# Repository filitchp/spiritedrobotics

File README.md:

# SantaBarBot Progress 

##Jan 21 2013
	
### Done:
- Breadboarded avr,
- Driving LED strip
- Driving PWM

### ToDo:
- Ron: protocol
- Dan: schematic
- Ryan: state machine + motor driver on breadboard

- Get crystal
- Raspi,
- Webserver
- Communication working
- Board Layout

## Nov 18 2012

Todo:
- Figure out motor driving
	- PWM direction or enable
- Start prototyping on the avr
	- Get powersupply and breadboard header
- Figure out if we want 1 or 2 uarts
	- Driving uart with raspberry pi
		- Can we directly use the onboard ethernet?
- Select avr chip (based on requirements)
	- Order a few of the them in a dip package for prototyping
- Meet Tuesday at 11.
	- Email invite to everyone
		
- Get everyone on google code group
	- Setup email notifications when commits made

- Setup irc chatroom.

- Ideas:
	
	- Use single bus with a buffer that can be disabled
		- Buffer keep signal strong over long distances
		- Enable allows us to determine the order of towers on the network
	- Semi-circle tower configuration
	- Towers modular
	- Sync spray to music / lights (bellagio)
	- Lazy susan to move cup into firing range and to customer
		- Doesn't have to be full circle. could be single beam with counter weight or multiple beams with cups on end (spokes of tire)spoke could have hole that cup would drop into
		- Rubber washer to set height and adjut for different cup sizes
	- Cup loader could drop cups on to lazy susan, or uses arm to grab cup and set it on the lazy susan
	
	- Ice machine? relay to control the dispensing of ice?
		- Digital scale to measure how much ice?

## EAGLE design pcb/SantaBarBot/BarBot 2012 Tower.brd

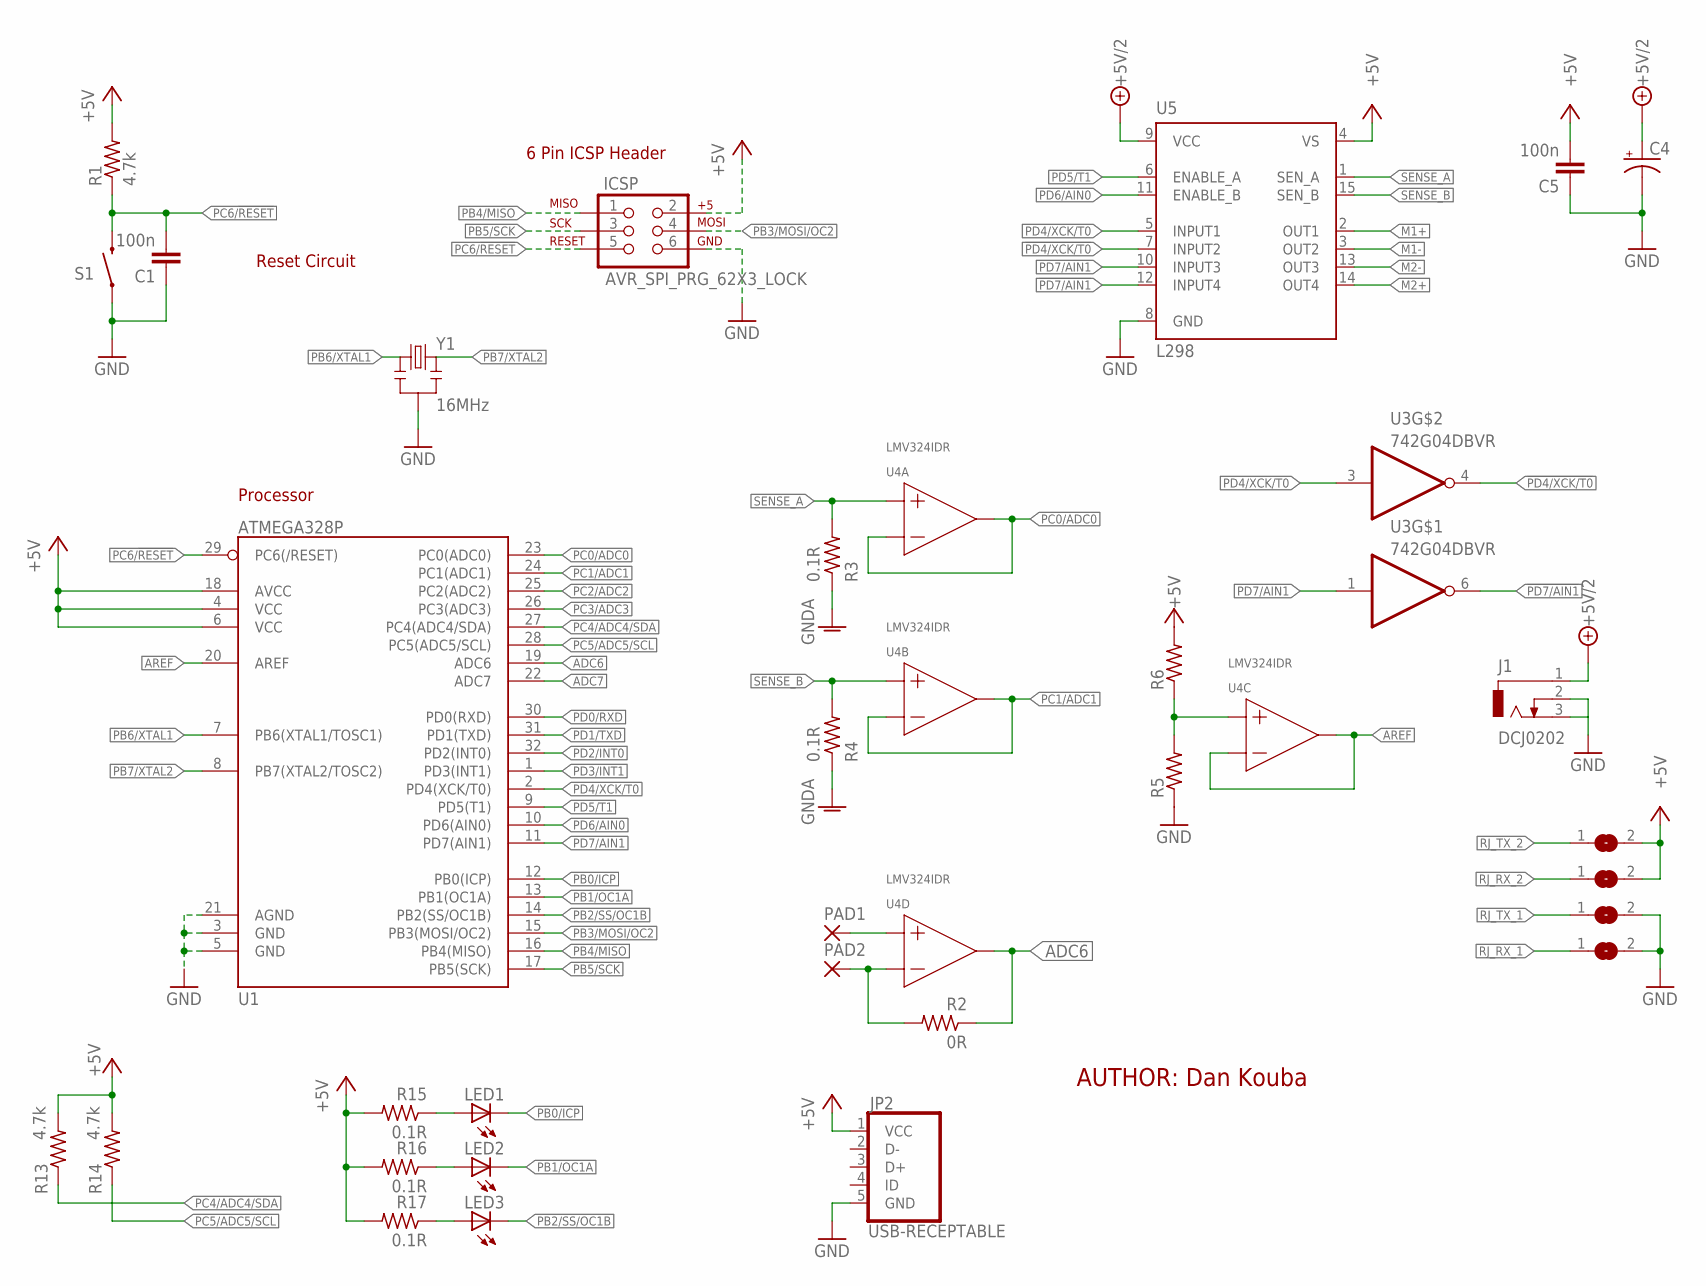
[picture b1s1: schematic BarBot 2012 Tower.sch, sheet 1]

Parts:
C1, C5: 100n; C0805
C4: CPOL-USE3.5-8; E3,5-8
ICSP: AVR_SPI_PRG_62X3_LOCK; 2X3_LOCK
J1: DCJ0202
JP2: USB-RECEPTABLE; FCI-10103594-0001LF
LED1, LED2, LED3: LEDCHIPLED_0805; CHIPLED_0805
PAD1, PAD2: 1,6/0,8
R1: 4.7k; R0805
R2: 0R; R0805; DIGIKEY_PN RHM.10MCT-ND
R3, R4, R15, R16, R17: 0.1R; R0805; DIGIKEY_PN RHM.10MCT-ND
R5, R6: R-US_R0805; R0805
R13, R14: 4.7k; R0805; DIGIKEY_PN RHM.10MCT-ND
S1: SWITCH-MOMENTARY-2PTH; TACTILE-PTH
SJ1, SJ2, SJ3, SJ4: SJ
U1: ATMEGA328P; TQFP32-08
U3: 742G04DBVR; DBV_R-PDSO-G6
U4: LMV324IDR; SO14
U5: L298; MULTIWATT-15
Y1: 16MHz; RESONATOR-SMD

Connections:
!PD4/XCK/T0: U3.4 (O), U5.7 (INPUT2)
!PD7/AIN1: U3.6 (O), U5.12 (INPUT4)
+5V: C5.2, ICSP.2, JP2.1 (VCC), R1.2, R6.2, R13.2, R14.2, R15.2, R16.2, R17.2, SJ3.2, SJ4.2, U1.4 (VCC), U1.6 (VCC), U1.18 (AVCC), U5.4 (VS); also elsewhere on the board
+5V/2: C4.+, J1.1, U5.9 (VCC); also elsewhere on the board
ADC6: R2.1, U1.19 (ADC6), U4.14 (OUT)
ADC7: U1.22 (ADC7)
AREF: U1.20 (AREF), U4.8 (OUT), U4.9 (-IN)
GND: C1.1, C4.-, C5.1, ICSP.6, J1.2, J1.3, JP2.5 (GND), R3.1, R4.1, R5.1, S1.1, SJ1.2, SJ2.2, U1.3 (GND), U1.5 (GND), U1.21 (AGND), U5.8 (GND), Y1.2; also elsewhere on the board
M1+: U5.2 (OUT1); also elsewhere on the board
M1-: U5.3 (OUT2); also elsewhere on the board
M2+: U5.14 (OUT4); also elsewhere on the board
M2-: U5.13 (OUT3); also elsewhere on the board
unnamed: LED1.A, R15.1
unnamed: PAD2.1, R2.2, U4.13 (-IN)
unnamed: LED2.A, R16.1
unnamed: LED3.A, R17.1
unnamed: R5.2, R6.1, U4.10 (+IN)
PB0/ICP: LED1.C, U1.12 (PB0(ICP))
PB1/OC1A: LED2.C, U1.13 (PB1(OC1A))
PB2/SS/OC1B: LED3.C, U1.14 (PB2(SS/OC1B))
PB3/MOSI/OC2: ICSP.4, U1.15 (PB3(MOSI/OC2))
PB4/MISO: ICSP.1, U1.16 (PB4(MISO)); also elsewhere on the board
PB5/SCK: ICSP.3, U1.17 (PB5(SCK)); also elsewhere on the board
PB6/XTAL1: U1.7 (PB6(XTAL1/TOSC1)), Y1.1
PB7/XTAL2: U1.8 (PB7(XTAL2/TOSC2)), Y1.3
PC0/ADC0: U1.23 (PC0(ADC0)), U4.1 (OUT), U4.2 (-IN)
PC1/ADC1: U1.24 (PC1(ADC1)), U4.6 (-IN), U4.7 (OUT)
PC2/ADC2: U1.25 (PC2(ADC2))
PC3/ADC3: U1.26 (PC3(ADC3))
PC4/ADC4/SDA: R13.1, U1.27 (PC4(ADC4/SDA))
PC5/ADC5/SCL: R14.1, U1.28 (PC5(ADC5/SCL))
PC6/!RESET: C1.2, ICSP.5, R1.1, S1.3 (2), U1.29 (PC6(/RESET))
PD0/RXD: U1.30 (PD0(RXD)); also elsewhere on the board
PD1/TXD: U1.31 (PD1(TXD)); also elsewhere on the board
PD2/INT0: U1.32 (PD2(INT0))
PD3/INT1: U1.1 (PD3(INT1))
PD4/XCK/T0: U1.2 (PD4(XCK/T0)), U3.3 (I), U5.5 (INPUT1)
PD5/T1: U1.9 (PD5(T1)), U5.6 (ENABLE_A)
PD6/AIN0: U1.10 (PD6(AIN0)), U5.11 (ENABLE_B)
PD7/AIN1: U1.11 (PD7(AIN1)), U3.1 (I), U5.10 (INPUT3)
RJ_RX_1: SJ2.1; also elsewhere on the board
RJ_RX_2: SJ4.1; also elsewhere on the board
RJ_TX_1: SJ1.1; also elsewhere on the board
RJ_TX_2: SJ3.1; also elsewhere on the board
SENSE_A: R3.2, U4.3 (+IN), U5.1 (SEN_A)
SENSE_B: R4.2, U4.5 (+IN), U5.15 (SEN_B)
TP1: PAD1.1, U4.12 (+IN)

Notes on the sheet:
Reset Circuit
6 Pin ICSP Header
Processor
AUTHOR: Dan Kouba

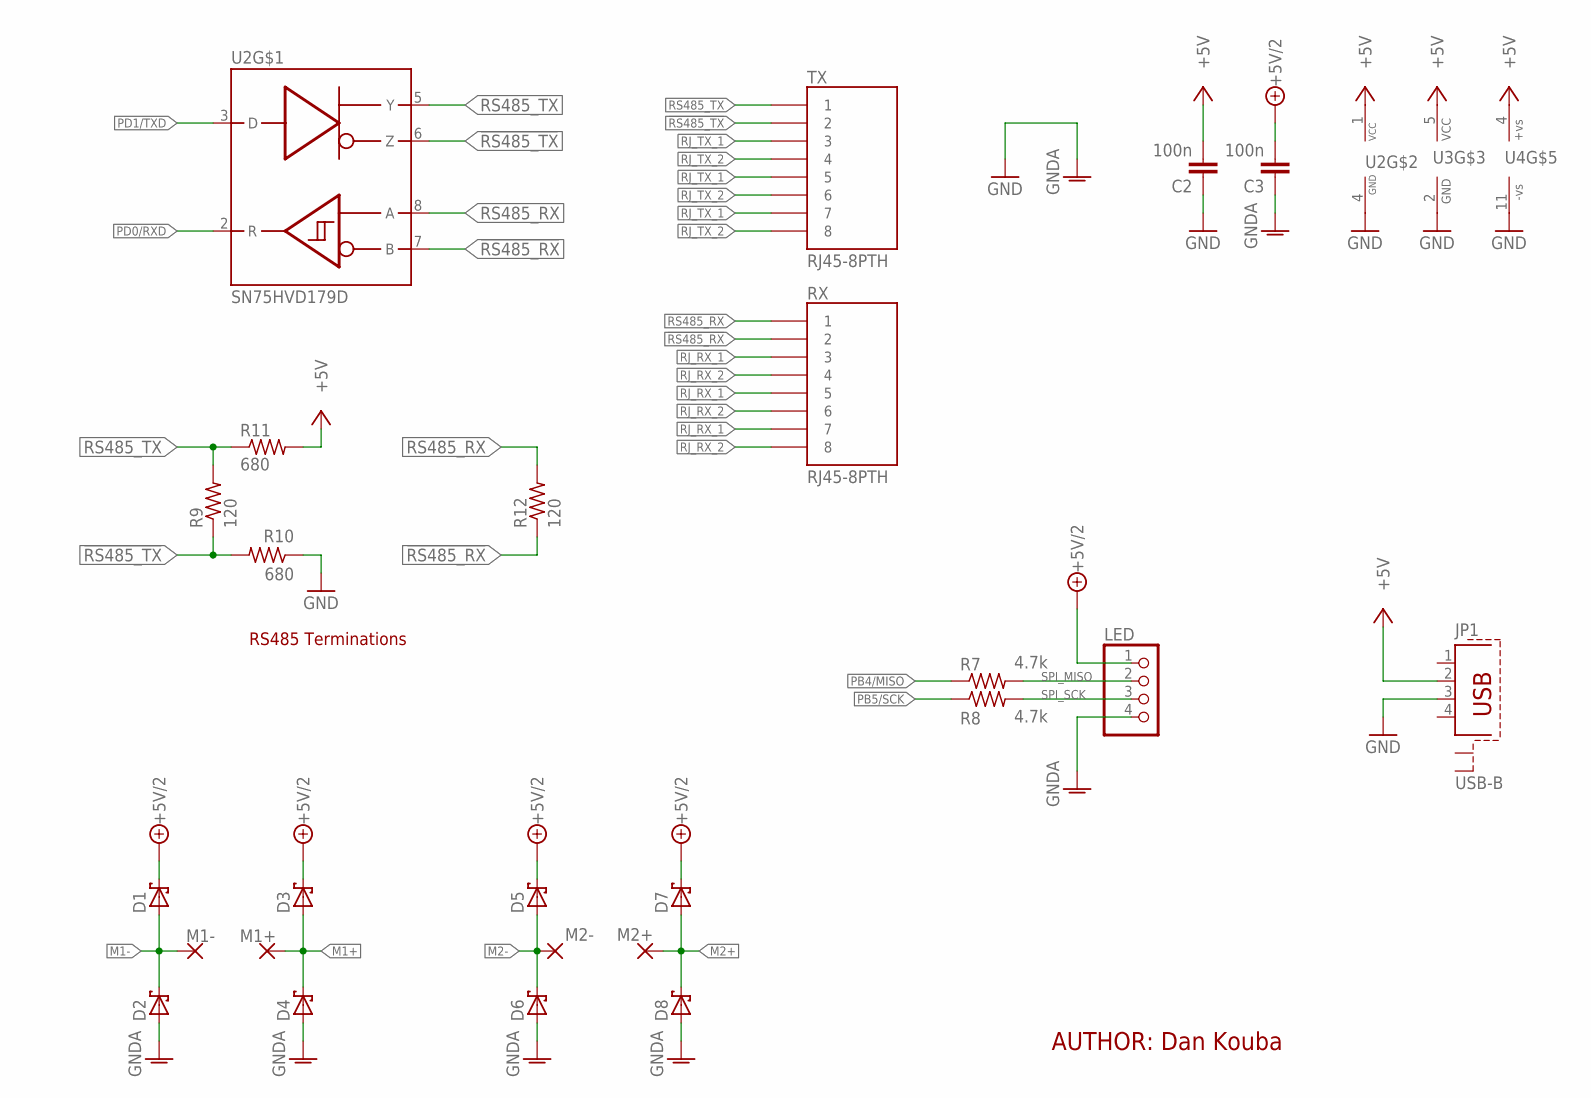
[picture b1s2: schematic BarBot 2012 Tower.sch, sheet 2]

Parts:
C2, C3: 100n; C0805
D1, D2, D3, D4, D5, D6, D7, D8: SCHOTTKY-DIODESMD; SMB; DIGIKEY_PN S320FSCT-ND
JP1: USB-B; PN61729-S
LED: PINHD-1X4; 1X04
M1+, M1-, M2+, M2-: 3,81/1,1
R7, R8: 4.7k; R0805
R9, R12: 120; R0805
R10, R11: 680; R0805
RX: RJ45-8PTH; RJ45-8
TX: RJ45-8PTH; RJ45-8
U2: SN75HVD179D; SO-08
U3: 742G04DBVR; DBV_R-PDSO-G6
U4: LMV324IDR; SO14

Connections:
!RS485_RX: R12.1, RX.2, U2.7 (B)
!RS485_TX: R9.1, R10.2, TX.2, U2.6 (Z)
+5V: C2.2, JP1.2, R11.2, U2.1 (VCC), U3.5 (VCC), U4.4 (+VS); also elsewhere on the board
+5V/2: C3.2, D1.C, D3.C, D5.C, D7.C, LED.1; also elsewhere on the board
GND: C2.1, C3.1, D2.A, D4.A, D6.A, D8.A, JP1.3, LED.4, R10.1, U2.4 (GND), U3.2 (GND), U4.11 (-VS); also elsewhere on the board
M1+: D3.A, D4.C, M1+.1; also elsewhere on the board
M1-: D1.A, D2.C, M1-.1; also elsewhere on the board
M2+: D7.A, D8.C, M2+.1; also elsewhere on the board
M2-: D5.A, D6.C, M2-.1; also elsewhere on the board
PB4/MISO: R7.1; also elsewhere on the board
PB5/SCK: R8.1; also elsewhere on the board
PD0/RXD: U2.2 (R); also elsewhere on the board
PD1/TXD: U2.3 (D); also elsewhere on the board
RJ_RX_1: RX.3, RX.5, RX.7; also elsewhere on the board
RJ_RX_2: RX.4, RX.6, RX.8; also elsewhere on the board
RJ_TX_1: TX.3, TX.5, TX.7; also elsewhere on the board
RJ_TX_2: TX.4, TX.6, TX.8; also elsewhere on the board
RS485_RX: R12.2, RX.1, U2.8 (A)
RS485_TX: R9.2, R11.1, TX.1, U2.5 (Y)
SPI_MISO: LED.2, R7.2
SPI_SCK: LED.3, R8.2

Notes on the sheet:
RS485 Terminations
AUTHOR: Dan Kouba

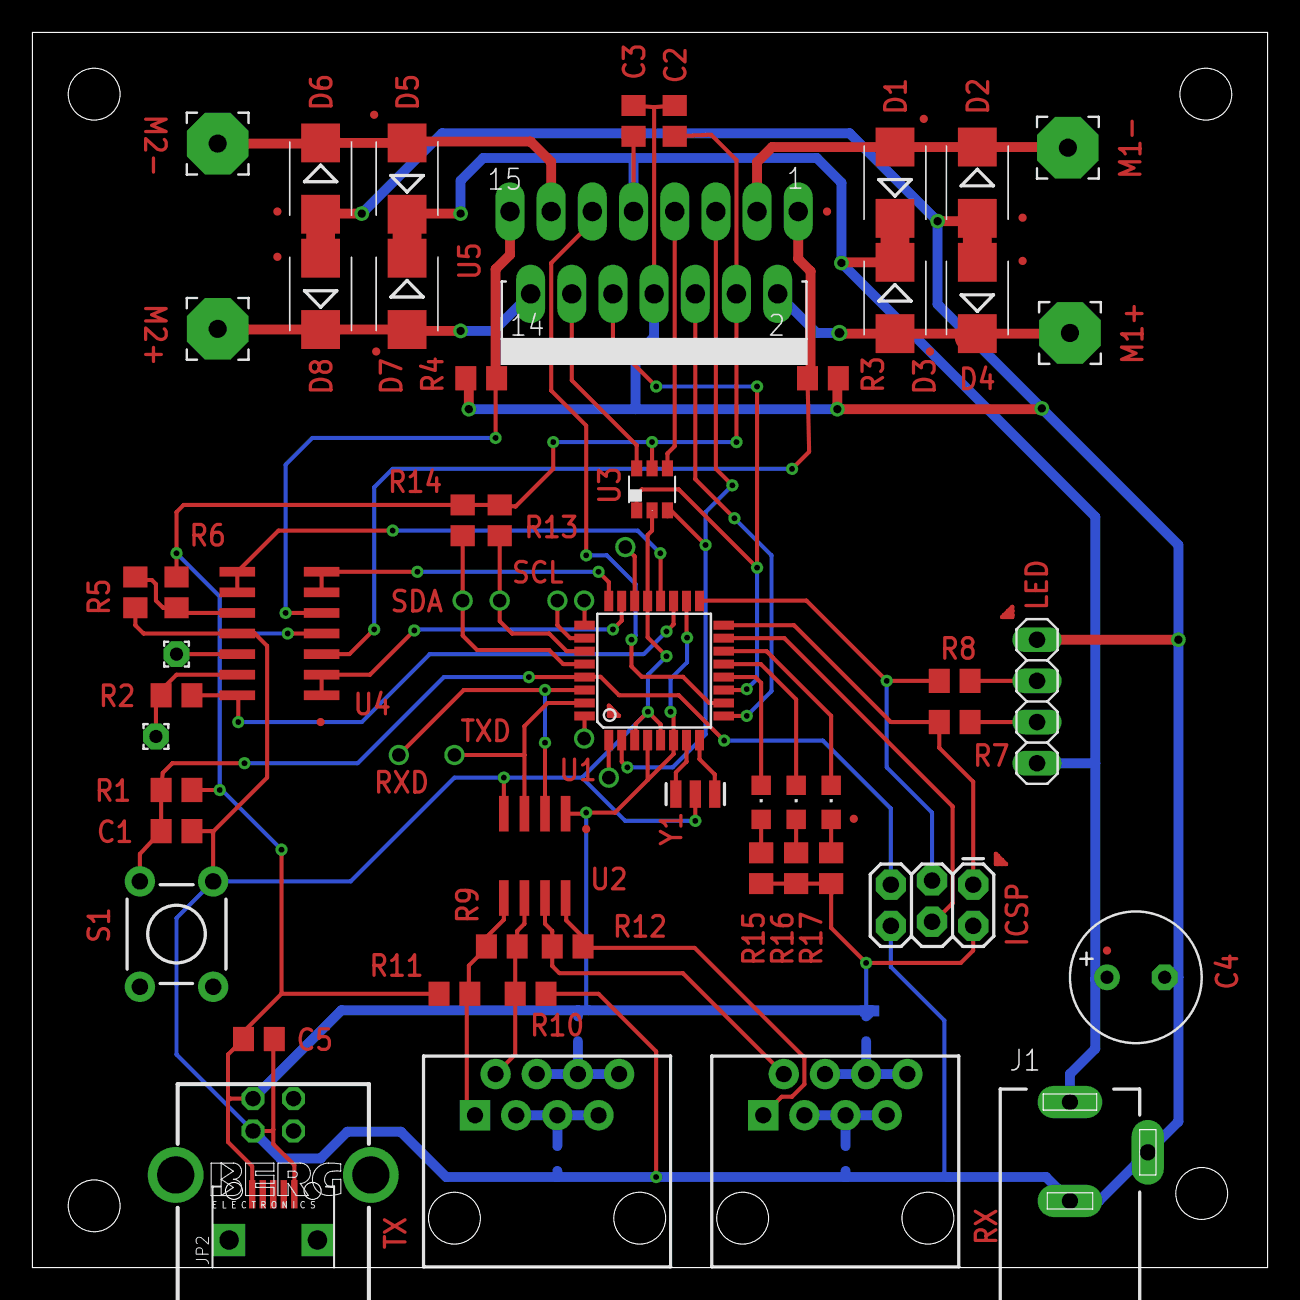
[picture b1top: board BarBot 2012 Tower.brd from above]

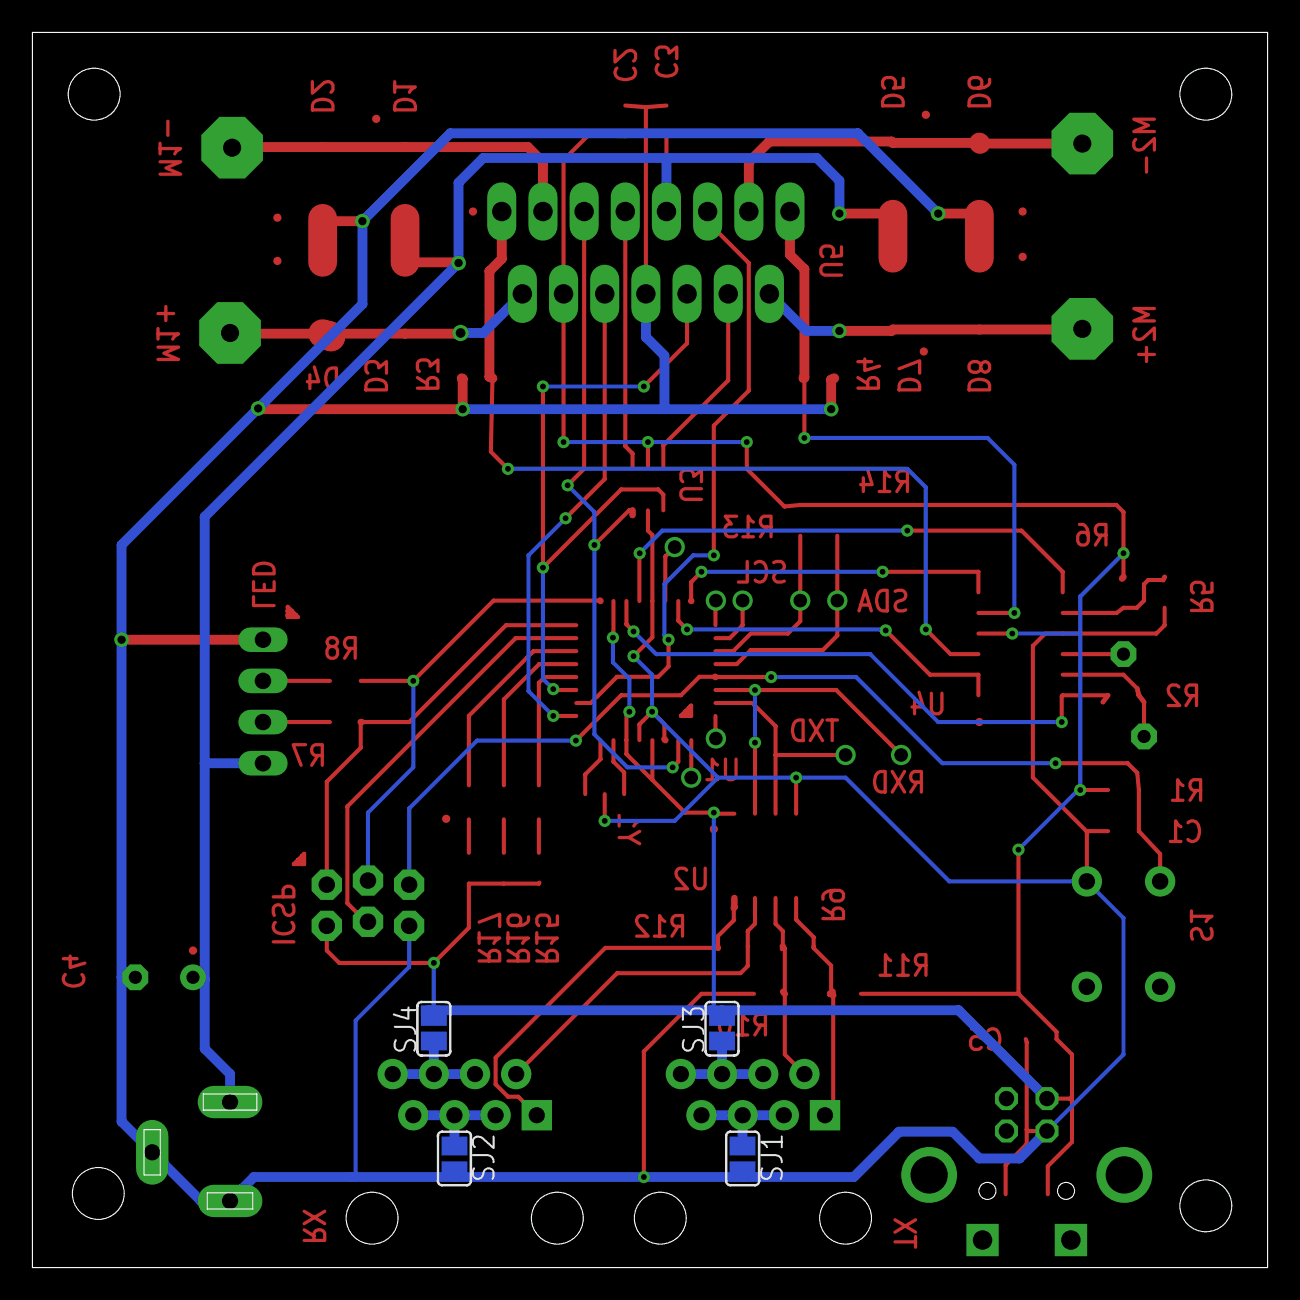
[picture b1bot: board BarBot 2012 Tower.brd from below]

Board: 2 copper layers, 76.2 x 76.2 mm, 57 parts (4 on the bottom side), 48 nets.

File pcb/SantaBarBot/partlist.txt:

Partlist

Exported from BarBot 2012 Tower.sch at 2/10/2013 10:12:03 PM

EAGLE Version 6.3.0 Copyright (c) 1988-2012 CadSoft

Assembly variant: 

Part     Value                 Device                Package         Library                    Sheet

C1       100n                  C-EUC0805             C0805           rcl                        1
C2       100n                  C-EUC0805             C0805           rcl                        2
C3       100n                  C-EUC0805             C0805           rcl                        2
C4                             CPOL-USE3.5-8         E3,5-8          rcl                        1
C5       100n                  C-EUC0805             C0805           rcl                        1
D1                             SCHOTTKY-DIODESMD     SMB             diode                      2
D2                             SCHOTTKY-DIODESMD     SMB             diode                      2
D3                             SCHOTTKY-DIODESMD     SMB             diode                      2
D4                             SCHOTTKY-DIODESMD     SMB             diode                      2
D5                             SCHOTTKY-DIODESMD     SMB             diode                      2
D6                             SCHOTTKY-DIODESMD     SMB             diode                      2
D7                             SCHOTTKY-DIODESMD     SMB             diode                      2
D8                             SCHOTTKY-DIODESMD     SMB             diode                      2
ICSP     AVR_SPI_PRG_62X3_LOCK AVR_SPI_PRG_62X3_LOCK 2X3_LOCK        SparkFun-Connectors        1
J2       POWER_JACKSLT         POWER_JACKSLT         POWER_JACK_SLOT SparkFun-Connectors        2
JP1      USB-B                 PN61729-S             PN61729-S       con-berg                   2
LED                            PINHD-1X4             1X04            pinhead                    2
LED1                           LEDCHIPLED_0805       CHIPLED_0805    led                        1
LED2                           LEDCHIPLED_0805       CHIPLED_0805    led                        1
LED3                           LEDCHIPLED_0805       CHIPLED_0805    led                        1
M1+                            3,81/1,1              3,81/1,1        wirepad                    2
M1-                            3,81/1,1              3,81/1,1        wirepad                    2
M2+                            3,81/1,1              3,81/1,1        wirepad                    2
M2-                            3,81/1,1              3,81/1,1        wirepad                    2
PAD1                           1,6/0,8               1,6/0,8         wirepad                    1
PAD2                           1,6/0,8               1,6/0,8         wirepad                    1
R1       4.7k                  R-US_R0805            R0805           rcl                        1
R2       0R                    R-US_R0805            R0805           rcl                        1
R3       0.1R                  R-US_R0805            R0805           rcl                        1
R4       0.1R                  R-US_R0805            R0805           rcl                        1
R5                             R-US_R0805            R0805           rcl                        1
R6                             R-US_R0805            R0805           rcl                        1
R7       4.7k                  R-US_R0805            R0805           rcl                        2
R8       4.7k                  R-US_R0805            R0805           rcl                        2
R9       120                   R-US_R0805            R0805           rcl                        2
R10      680                   R-US_R0805            R0805           rcl                        2
R11      680                   R-US_R0805            R0805           rcl                        2
R12      120                   R-US_R0805            R0805           rcl                        2
R13      4.7k                  R-US_R0805            R0805           rcl                        1
R14      4.7k                  R-US_R0805            R0805           rcl                        1
R15      0.1R                  R-US_R0805            R0805           rcl                        1
R16      0.1R                  R-US_R0805            R0805           rcl                        1
R17      0.1R                  R-US_R0805            R0805           rcl                        1
RX       RJ45-8PTH             RJ45-8PTH             RJ45-8          SparkFun-Connectors        2
S1       SWITCH-MOMENTARY-2PTH SWITCH-MOMENTARY-2PTH TACTILE-PTH     SparkFun-Electromechanical 1
TX       RJ45-8PTH             RJ45-8PTH             RJ45-8          SparkFun-Connectors        2
U1       ATMEGA328P            ATMEGA328_SMT         TQFP32-08       SparkFun-DigitalIC         1
U2       SN75HVD179D           SN75HVD179D           SO-08           texas                      2
U3       742G04DBVR            742G04DBVR            DBV_R-PDSO-G6   74xx-little-us             1
U4       LMV324IDR             LMV324IDR             SO14            bb_parts_OpAmp             1
U5       L298                  L298                  MULTIWATT-15    st-microelectronics        1
Y1       16MHz                 RESONATOR16MHZ        RESONATOR-SMD   SparkFun-FreqCtrl          1

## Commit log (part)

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2013-01-28 removed os x files
2013-01-28 adding drink json file
2013-01-28 Adding menus barebones
2013-01-28 minor styling mods
2013-01-28 Added boost example HTTP server files
2013-01-28 Removing rendered alert
2013-01-28 This is a better place to fetch
2013-01-28 minor ui tweaks
2013-01-28 adding c++ webserver
2013-01-28 Breaking out model js
2013-01-28 Minor Typo
2013-01-28 Using underscore templates for drink menu
2013-01-29 Adding old SVN stuff from Ryan, plus my new PCB files
2013-01-29 Created new component for dual invert chip. Mostly done with motor driver, need to add sense resistors. Added SPI buffer resistors
2013-01-29 Menu styling. Removed unneeded js
2013-01-29 Addition to drink JSON list. Using local jQuery
2013-01-31 Created v0.001 of Serial Command Protocol
    This is an early version of the serial command protocol. It does not have the general list of commands. This document covers the basic message formatting and network address reassignment to allow mod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
2013-01-31 - Made symbol for dual NOT gate - Made symbol for bus tranceiver - Placed network components - Finished motor driver - Added sense resistors and buffer op-amps - Also added buffer op-amp for AREF on 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
2013-01-31 Playing with readmes within folder structure
2013-01-31 Playing with readmes again
2013-01-31 Update avr/Serial Command Protocol Spec v0.001
    Created subsection for general call address. Added behavior for messages using the general call address.
    This allows us to propagate commands through the whole network without having to write a specific propagation handler for each one.
    Example: A "halt node" command sent to the general call address will propagate to every node in the network, acting as a "halt all nodes" command.
2013-02-01 Started PCB layout, cleaning up schematic. Added RS485 termination, fixed duplicate chips
2013-02-02 Finished routing PCB, added PDFs of board and schematic to directory, generated netlist, pinlist, and partslist for design
2013-02-02 Changed board to 2 layers, 3x3 inches. Fully routed, DRC and ERC run, all errors corrected. PDFs generated
2013-02-02 Added prototypes for order and category models, added a stub response for available categories, updated the menu topbar to pull from categories
2013-02-10 Added system diagram
2013-02-11 Fixed component IDs so they don't violate clearance requirements, made them smaller. Routed extra opamp to unused ADC pin.
2013-02-11 Board ready for review. Rendered in 3D, see board_render.png. Netlist/pinlist/partlist/pdfs updated
2013-02-12 Finalizing PCB. Added DC over ethernet capability, added micro-usb connector footprint, changed power jack to more standard one. Added mounting holes. Cleaned up some traces.
2013-02-16 tower mechanical
    (as posted on the google group) the Santa Barbot Tower 2.0 is ready for
    review!
    its pretty similar in form to last year's barbot. As this is my first 3d
    jigsaw design, i resisted temptations to get too crazy - but if this all
    works fine maybe we can experiment with some more daring shapes in the
    future.
2013-02-18 Added basic ability to read a drink library and system configuration to the server. Added corresponding assets and models
2013-02-19 Outputing valid JSON drink list to cout
2013-02-21 adding communication files
2013-02-23 Category title, not quite right but servicable
2013-02-23 Got web server to host menu and dynamically display drinks from configuration files
2013-02-23 Popup an order alert
2013-02-23 Basic looking modal
2013-02-23 Missed the tag on the button
2013-02-23 Server understands order drink message
2013-02-23 Putting topbar back
2013-02-23 Response parsed... basic decision
2013-02-23 Added ability to add and view orders
2013-02-23 Playing with the styles on the menu
2013-02-23 just couldn't put it down!
2013-02-24 Added ingredients to an order
2013-02-24 Still trying stuff out with the ingredients list
2013-02-26 rough start on communication protocol, storing data when it is for the specified node
2013-02-26 Drink approval code
2013-02-27 finishing initializing the uart
2013-02-27 adding blocking read
2013-02-27 setting correct ISR name, setting values to unsigned char
2013-02-27 adding tower c file. formatting
2013-02-27 Basic tower test functionality
2013-02-27 Reverting change to barbot.cpp
2013-02-27 reverting rereverting revert
2013-02-27 Admin testing console
2013-02-27 Basic serial output for uC test
2013-02-27 switching motor numbering to match board. setting up tower to run test communication code
2013-02-27 got led strips working with pcb. implemented better rainbow function. fix issue with pin description file
2013-02-28 modifying pin constraint to fix issue. doubling spi output speed.
2013-02-28 successfull communication
2013-02-28 lowering clock speed of LEDs, building up comm protocol
2013-02-28 dividing motor pwm clock by 8
2013-03-01 Error handling in the read code
2013-03-01 Additional serial io config options
2013-03-01 More serial debug code
2013-03-01 implemented mValidDrinks for Drink Manager Object. Menu.html displays valid drinks onlyclear
2013-03-01 Approved Drink orders now get stored in Records directory as Json files.
2013-03-01 Removed dialog message on successful tower test
2013-03-01 More drinks
2013-03-01 Correcting drink errors
2013-03-01 Minor clean up. Test tower amount is now in seconds
2013-03-01 starting on non blocking timed pump on
2013-03-02 Ability to normalize a drink and print ingredients
2013-03-02 Added tower init functionality:
2013-03-02 Init towers
2013-03-02 Removing drinks
2013-03-02 Known working init and test tower code
2013-03-02 First pass at modded rainbow light fantastic
2013-03-02 Andrew fixing andrews shitty code
2013-03-02 Added Amys wonderful drink list and images. Untested ability to order approved drink
2013-03-02 bonus straps
2013-03-02 Working modal
2013-03-02 motor now goes in reverse after pour
2013-03-02 motor commands now work with 2 bytes
2013-03-03 better server
2013-03-09 removing blocking delay, increasing reversing time for motor, adding test make file
2013-03-09 upping the baud to 115200
2013-03-09 Redesign of menu page well underway
2013-03-23 modified recipes and scaling for BarBot 2013
2013-03-23 Stripping down and building out
2013-03-23 Buttons in the right place, going to do the left nav
2013-03-23 Side menu is semi-in-place
2013-03-23 Styling, some spacers, now just to hook them up
2013-03-23 Server update. Logging is much more robust. Added more logs.
2013-03-23 Last commit before sleep
2013-03-23 Adjust light timing and up the baud
2013-03-28 Committing drink logs
2013-04-06 Update README.creole
    Updated readme
2013-04-07 Update README.creole
    Added features description
2013-04-07 Added order server build instructions
2013-04-07 Adding stop command to admin panel
2013-04-07 Caching, improved styling, a working stop button, and other nice things
2013-04-07 Better menu behavior and admin refreshes
2013-04-07 updates after discussion with paul
2013-04-07 Implemented halt towers command
2013-04-08 refactoring
2013-04-08 adding error light reset
2013-04-08 Removed legacy arduino code
2013-04-08 Fixed halt tower bug
2013-04-10 tweak
2013-04-10 Added Atmel Studio 6 Project for Tower App
    This project will build within Atmel Studio 6, allowing for development
    on windows, and/or running the device in the AVR simulator.
2013-04-10 added a /setTowerReverseTime route
2013-04-10 Added space drinks and images
2013-04-10 setting default reversing time. adding set pwm for testing make file
2013-04-11 Consolidated Tower Code
    Previously, windows IDE being used to build looked at different copies
    of the tower code.
    There will now be only one copy of the code, which both the linux and
    windows developers
    will look at.
2013-04-11 graphics
    made a folder for all graphicy stuff. put andrews cards in there and the
    logo i did
2013-04-11 removing magic number
2013-04-11 Space drink update
2013-04-11 Code Cleanup and Refactoring
    Specified variable bit length, updated code to conform with style.
2013-04-11 Rewrote led control code, added command to set led pattern
    Communication now supports an additional command: set LED pattern.
    Currently implemented patterns: all red, all green, all blue, all off,
    and the error pattern of a single red LED being on.
2013-04-11 Added lime juice changed drink towers for Yuri
2013-04-11 adjusting space drink recipes
2013-04-11 Adding solar flare
2013-04-11 logo color simplification for printing
2013-04-11 logo correction for simplification
2013-04-11 simple logo svg
2013-04-12 Added blue and green versions of the logo
2013-04-12 Put circle around blue version of logo
2013-04-12 Added tshirt logo
2013-04-12 New constants
2013-04-12 redesigned card logo latest logo
2013-04-12 Updated drink menu
2013-04-12 Adding video.js
2013-04-12 updating led code
2013-04-12 Adding another max video
2013-04-12 Another small video
2013-05-25 Finally pushing these changes and logs
2013-08-12 Test run in Paul's garage
2013-08-19 Logs labeled debug when generated without serial communication
2013-08-19 Reworked code to use timers
2013-08-19 Added shortcut to admin console
2013-08-20 Minor menu clean-up and bug fixes
2013-08-20 Prevent refresh after submitting drink
2013-08-21 Fixed issues with halt command. Rearranged some elements in admin console
2013-08-21 Re-added refresh after ordering (now I know why it was there). Computed timing to match lighting
2013-08-22 Minor admin UI styling tweaks. System busy checks. Added ability to trigger light routines from admin console
2013-08-22 Fixed some lighting issues. Refactoring, reorganization, commenting
2013-08-23 Added Oswald fonts. Minor styling tweaks
2013-08-24 Styling mods
2013-08-25 More config files
2013-08-26 Added logs from Paul's bday
2013-09-02 Sky's new UI design
2013-09-02 Reworked options/arguments. Added demo mode
2013-09-02 Updated readme with better setup instructions
2013-09-02 Fixed minor formatting issue in readme
2013-10-07 Added CC images and image attribution file
2013-10-07 Changed config file for testing
2013-10-08 logs from Pauls october beta testing. Modified blackhole recipe
2013-10-09 More drink images. Additional image replacements
2013-10-12 Image clean-up. Added new drink. Added some categories to drinks
2013-10-12 Alert on order approval
2013-10-14 Orders from Randys party. Modified pan galactic for ingredient set
2013-10-17 added new tower configuration
2013-10-17 adjusted barbot tower config
2013-10-18 Added new recipes, updated types and categories, added new type and new category of Classics
2013-10-21 Fixed minor typo
2013-10-21 Added support for two new drink types. Minor formatting on recipes
2013-10-21 Removed duplicate recipes
2013-10-22 bootstrap 3
2013-10-22 Tweaked drink recipes and order server for event
2013-10-22 remove refresh on modal accept
2013-10-22 Restored fonts
2013-10-24 Tuning styling and doing a piece for max
2013-10-24 Removing a few swp files
2013-10-24 Drink list now outputting attributions
2013-10-24 Clean up
2013-10-24 Drink confirmation messages and splash
2013-10-24 More drink messages and an attribution popover
2013-10-26 Have a working js
2013-10-26 starting on test buttons -AB
2013-11-02 On the fly changes for SF event
2013-11-02 Log files for SF event
2013-12-09 New orders from beta testing
2014-06-30 adding drinks for wedding. need pics
2014-07-01 Formatting and ingredient fixes. Setup barbot.json file for wedding
2014-07-01 Added pan galactic wedding blaster
2014-07-07 Wedding preparations. Polishing.
2014-07-07 Minor tweak
2014-08-24 Logs from the wedding
2014-08-30 Birthday menu
2014-08-30 New event-based timing queue. Work in progress
2014-08-30 Added ability to play music. Work in progress
2014-08-30 Pan galactic tweaks
2014-08-30 More routines
2014-08-30 Redid pan galactic routine and created catch all routine
2014-08-31 Logs from bday
2016-07-09 Added missing brackets around if statement.
2016-07-09 Adding lloyd code
    Adding our buddy lloyd
    Delete giant video files
2016-07-10 Rotating videos
2016-07-10 Adding compressed video
2016-07-10 4 more videos
2016-07-10 text rotation... not total
2016-07-10 Add trump and pangala
2016-07-10 Refactoring for tomorrow
2016-07-10 Drink intensity

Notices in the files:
parts and their libraries:
SparkFun-DigitalIC: Licensing: CC v3.0 Share-Alike You are welcome to use this library for commercial purposes.
